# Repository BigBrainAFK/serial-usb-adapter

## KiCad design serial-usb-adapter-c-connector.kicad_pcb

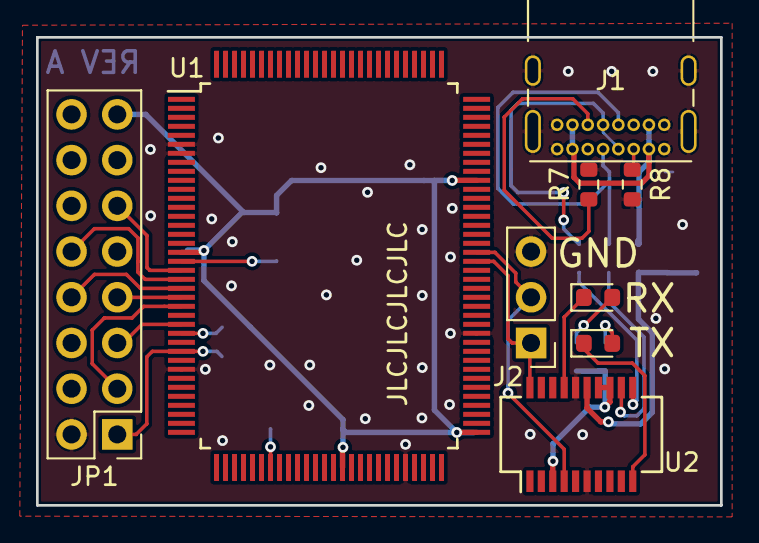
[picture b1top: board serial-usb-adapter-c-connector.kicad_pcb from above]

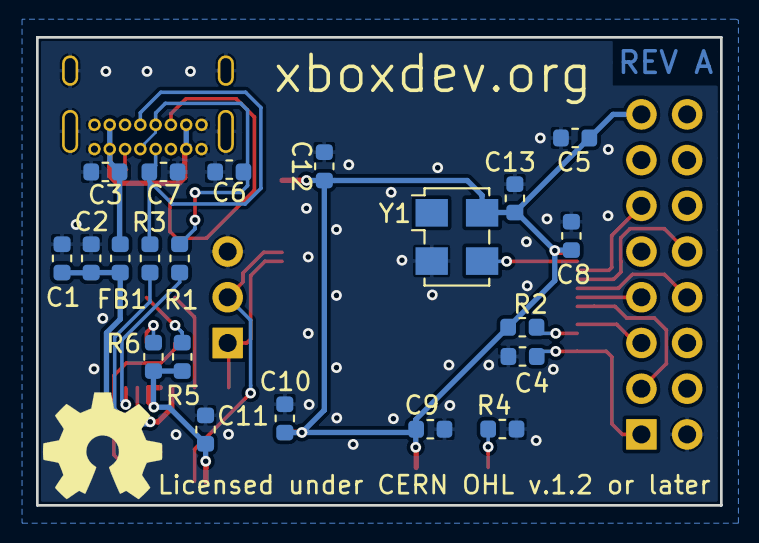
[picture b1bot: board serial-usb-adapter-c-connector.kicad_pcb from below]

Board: 2 copper layers, 38.0 x 26.0 mm, 31 parts (22 on the bottom side), 27 nets.

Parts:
C1: 4u7; C_0603_1608Metric
C2, C11: 100nF; C_0603_1608Metric
C3, C8, C9, C10, C12, C13: 10nF; C_0603_1608Metric
C4, C6, C7: 47pF; C_0603_1608Metric
C5: 10uF; C_0603_1608Metric
D1: Green; LED_0603_1608Metric
D2: Blue; LED_0603_1608Metric
FB1: 33ohm; L_0603_1608Metric
J1: USB_C_Receptacle_USB2.0; USB_C_Receptacle_GCT_USB4085
J2: UART Header; PinHeader_1x03_P2.54mm_Vertical
JP1: LPC; PinHeader_2x08_P2.54mm_Vertical
OSHW Logo: OSHW-Symbol_6.7x6mm_SilkScreen
R1, R3: 27R; R_0603_1608Metric
R2, R4: 10k; R_0603_1608Metric
R5: 470R; R_0603_1608Metric
R6: 1.2k; R_0603_1608Metric
R7, R8: 5.1k; R_0603_1608Metric
U1: LPC47M192; LQFP-128_14x20mm_P0.5mm
U2: FT231XS; SSOP-20_3.9x8.7mm_P0.635mm
Y1: SG5032CAN 14.318MHz; Oscillator_SMD_TXC_7C-4Pin_5.0x3.2mm_HandSoldering

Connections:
+3V3: C11.1, R5.1, R6.1, U2.3, U2.13, U2.14
unnamed: C3.1, FB1.1, J1.A4, J1.A9, J1.B4, J1.B9
unnamed: C4.1, JP1.1, U1.29
unnamed: C6.1, J1.A6, J1.B6, R1.2
unnamed: C7.1, J1.A7, J1.B7, R3.1
unnamed: D1.1, U2.10
unnamed: D1.2, R6.2
unnamed: D2.1, U2.17
unnamed: D2.2, R5.2
unnamed: J1.A5, R8.2
unnamed: J1.B5, R7.2
unnamed: J2.1, U1.84, U2.20
unnamed: J2.2, U1.85, U2.4
unnamed: JP1.3, U1.24
unnamed: JP1.5, U1.26
unnamed: JP1.7, U1.23
unnamed: JP1.8, U1.22
unnamed: JP1.10, U1.21
unnamed: JP1.11, U1.20
unnamed: R1.1, U2.11
unnamed: R2.1, U1.27
unnamed: R3.2, U2.12
unnamed: R4.1, U1.45
unnamed: U1.19, Y1.3
VBUS: C1.1, C2.1, FB1.2, U2.15
VCC: C5.2, C8.1, C9.1, C10.1, C12.1, C13.2, JP1.15, R2.2, U1.18, U1.53, U1.65, U1.93, Y1.4
VSS: C1.2, C2.2, C3.2, C4.2, C5.1, C6.2, C7.2, C8.2, C9.2, C10.2, C11.2, C12.2, C13.1, J1.A1, J1.A12, J1.B1, J1.B12, J1.S1, J2.3, JP1.2, R4.2, R7.1, R8.1, U1.6, U1.7, U1.31, U1.60, U1.76, U2.6, U2.16, Y1.2

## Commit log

2020-11-19 Add USB C Variant of the PCB
2020-11-20 Fixed FB1 position in schematic

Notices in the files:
serial-usb-adapter-c-connector.kicad_pcb:
Copyright Mike Davis 2019
Licensed under CERN OHL v.1.2 or later
